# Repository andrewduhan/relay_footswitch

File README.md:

# relay_footswitch
Control your amp's reverb with a low-voltage relay
================

Tap your 6.3V heater rail to control a relay - switch your reverb on and off with low-voltage DC, instead of sending your tone through a long antenna on the floor!

Designed as two break-apart boards, one to provide 5V DC from the 6.3VAC heater rail, and a breakout board for the DPDT relay.
Inputs and outputs are sized to accept turret lugs (tubedepot part "BP-TURRET").
Generate 5VDC and send it down the wire to your footswitch.  Leave your signal and tone where it belongs - inside your amp chassis.

#BOM
- relay:              Omron G6A-234P-ST-US-DC5
- big cap:            4700uF 35V Nichicon
- little cap:         Optional, whatever you want really
- bridge rectifier:   Rectron BR305 
- diode:              1N4001 
- vreg:               7805

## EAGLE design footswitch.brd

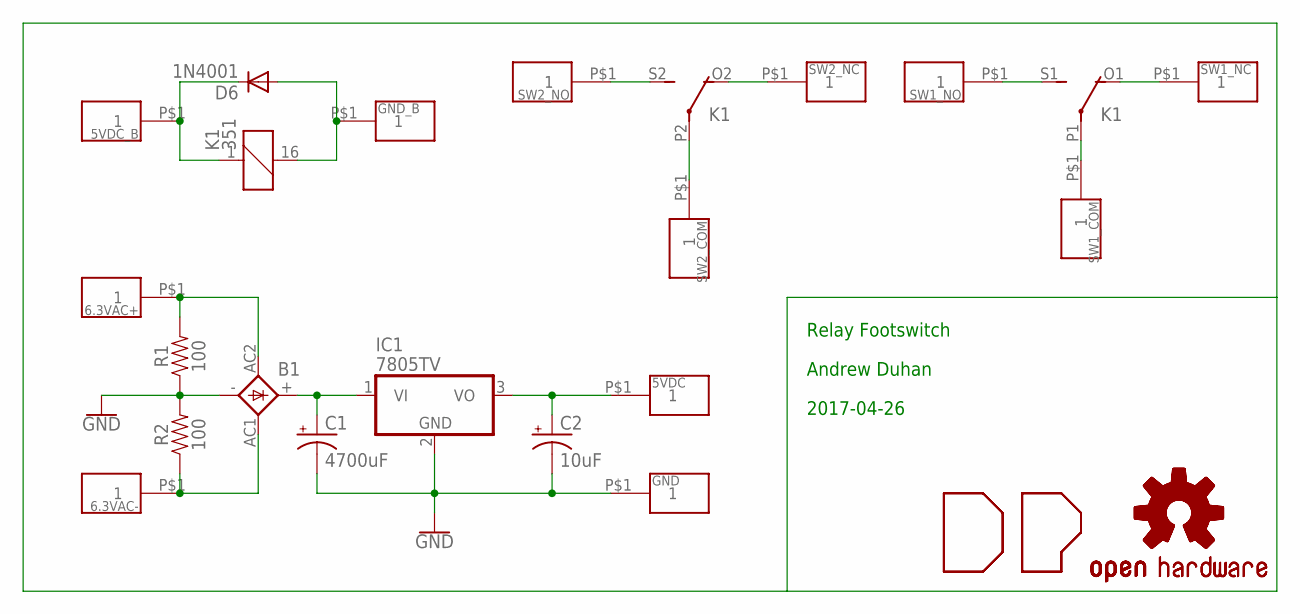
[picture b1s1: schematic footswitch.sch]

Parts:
5VDC, 5VDC_B, 6.3VAC+, 6.3VAC-: TURRET_LUG_1540
B1: GBU4; GBU4S
C1: 4700uF; E7,5-18
C2: 10uF; CPOL-RADIAL-2.5MM-5MM
D6: 1N4001; DO41-10
GND: TURRET_LUG_1540
GND_B: TURRET_LUG_1540
IC1: 7805TV; TO220V
K1: 351
LOGO1, LOGO2: OSHW-LOGOMINI; OSHW-LOGO-MINI
R1, R2: 100; AXIAL-0.3
SW1_COM, SW1_NC, SW1_NO, SW2_COM, SW2_NC, SW2_NO: TURRET_LUG_1540
U$1, U$2: DP_LOGO

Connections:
5VDC: 5VDC.P$1, C2.1 (+), IC1.3 (VO)
5VDC_B: 5VDC_B.P$1, D6.C, K1.1
GND: B1.-, C1.-, C2.2 (-), GND.P$1, IC1.2 (GND), R1.P$1 (1), R2.P$2 (2)
GND_B: D6.A, GND_B.P$1, K1.16 (2)
unnamed: B1.+, C1.+, IC1.1 (VI)
unnamed: 6.3VAC+.P$1, B1.AC2 (AC1), R1.P$2 (2)
unnamed: 6.3VAC-.P$1, B1.AC1 (AC2), R2.P$1 (1)
unnamed: K1.P2, SW2_COM.P$1
unnamed: K1.O2 (O), SW2_NC.P$1
unnamed: K1.S2 (S), SW2_NO.P$1
unnamed: K1.O1 (O), SW1_NC.P$1
unnamed: K1.S1 (S), SW1_NO.P$1
unnamed: K1.P1, SW1_COM.P$1

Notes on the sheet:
Relay Footswitch
Andrew Duhan
2017-04-26

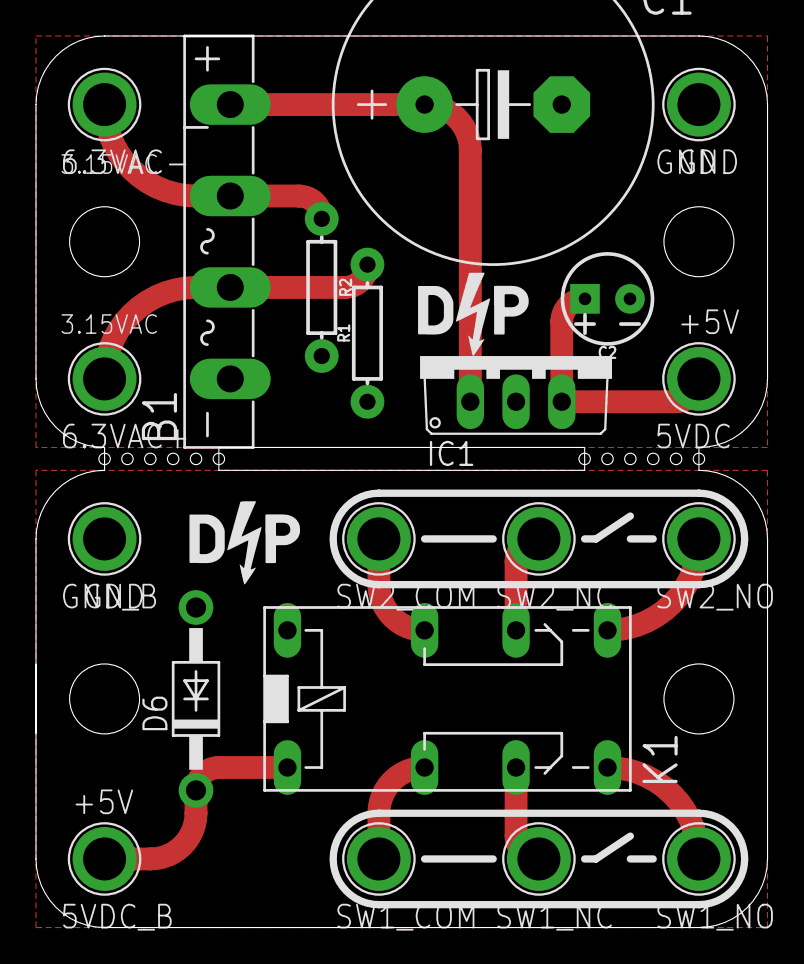
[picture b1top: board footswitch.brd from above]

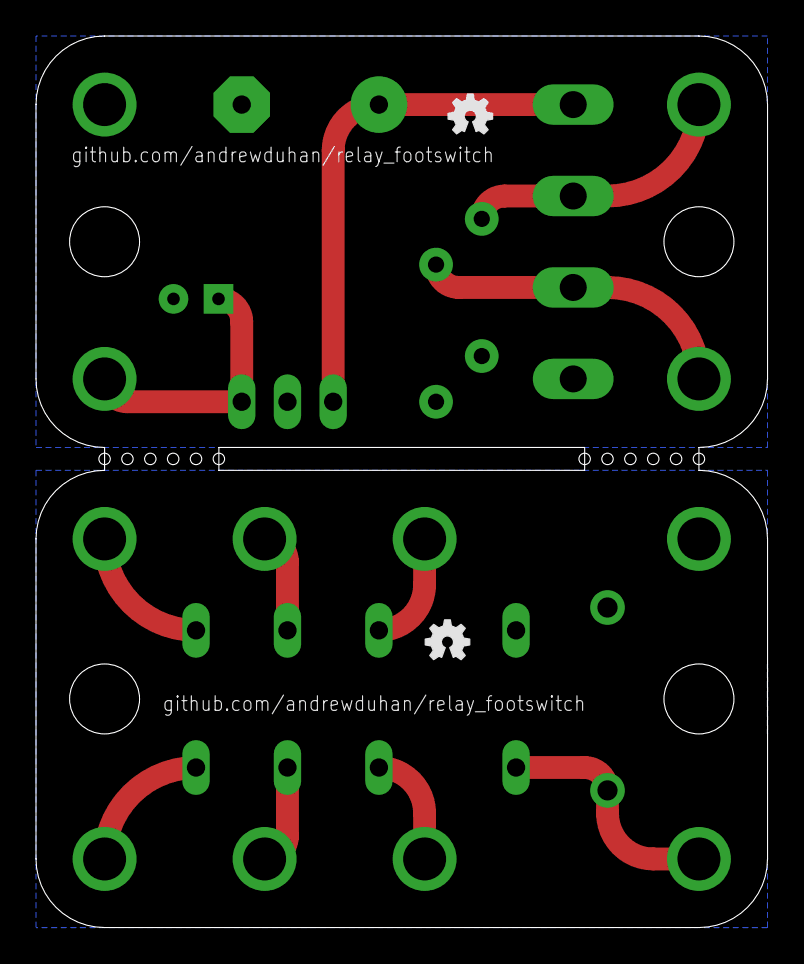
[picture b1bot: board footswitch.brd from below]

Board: 2 copper layers, 40.6 x 49.5 mm, 24 parts (2 on the bottom side), 13 nets.

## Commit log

2017-06-21 rev A
2017-06-21 readme formatting

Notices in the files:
parts and their libraries:
SparkFun-Resistors: Licensing: Creative Commons ShareAlike 4.0 International - https://creativecommons.org/licenses/by-sa/4.0
